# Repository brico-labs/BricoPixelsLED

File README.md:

# BricoPixels LED

PCB diseñanda por BricoLabs para utilizar en proyectos de e-textile. Se utiliza un LED RGB [WS2812B](assets/WS2812B.pdf) el cual incorpora un circuito de control dentro del propio componente, que es un encapsulado 5050.

Para utilizar junto con microcontroladores AVR de Atmel (ATmega, ATtiny) o con la familia ESP de Espressif (ESP8266, etc) 

Cada BricoPixel lleva tan solo dos componentes:

* LED RGB [WS2812B](https://www.tme.eu/es/details/ws2812b-b/leds-smd-de-colores/worldsemi/ws2812b-black/) con encapsulado de color negro.
* Condensador [SMD de 100nF 0805](https://www.tme.eu/es/details/08051c104kat2a/condensadores-mlcc-smd-0805/avx/), para estabilizar la tensión de alimentación del circuito de control del LED RGB.

<div style="text-align:center"></div>

La forma de la placa PCB está diseñada para poder coserla directamente sobre cualquier textil con hilo conductor, o incluso pegarla sobre otras superficies planas.

En el directorio *gerber* se encuentra la PCB ya panelizada y lista para fabricar, en placas de 10 x 10 cm y con 25 unidades de BricoPixel cada una. Para esto se utilizó el software [GerberTools](https://github.com/ThisIsNotRocketScience/GerberTools).

**Se recomienda un grosor de PCB menor o igual a 1 milímetro.** Esto facilita recortar manualmente cada uno de los BricoPixel.

<div style="text-align:center"></div>

----

Esta obra está bajo una [licencia de Creative Commons Reconocimiento 4.0 Internacional (CC-BY)](http://creativecommons.org/licenses/by/4.0/).

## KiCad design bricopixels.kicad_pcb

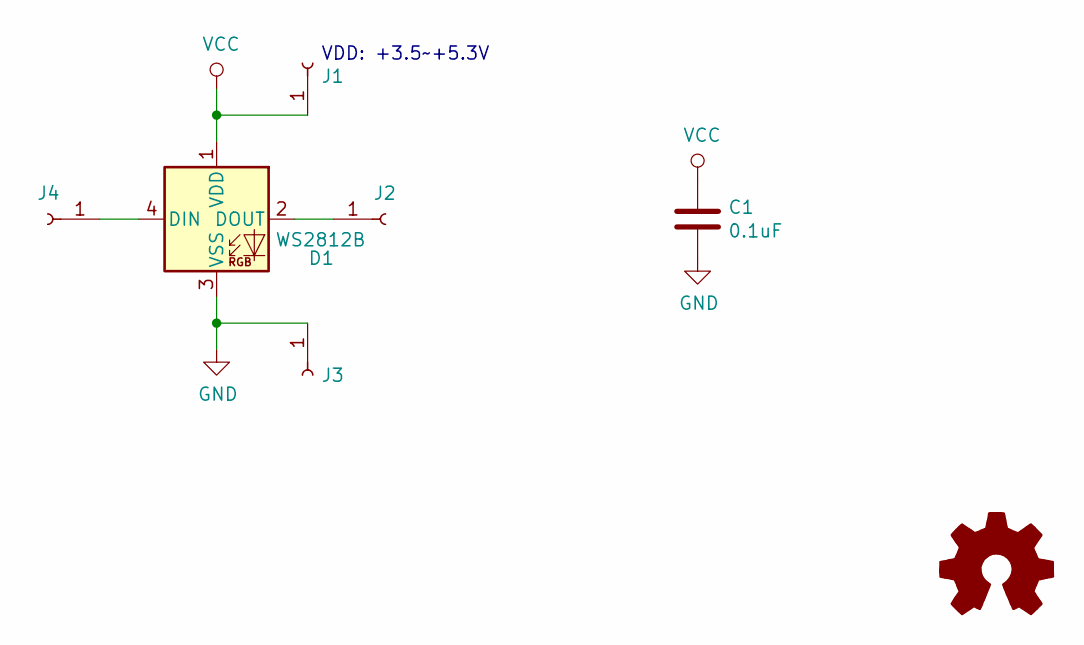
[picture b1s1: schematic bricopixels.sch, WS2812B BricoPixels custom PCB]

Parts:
C1: 0.1uF; C_0805_2012Metric
D1: WS2812B; LED_WS2812B_PLCC4_5.0x5.0mm_P3.2mm
J1, J2, J3, J4: Conn_01x01_Female; BricoPixel_pad_4x

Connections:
GND: C1.2, D1.3 (VSS), J3.1
unnamed: D1.2 (DOUT), J2.1
unnamed: D1.4 (DIN), J4.1
VCC: C1.1, D1.1 (VDD), J1.1

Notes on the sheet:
VDD: +3.5~~+5.3V

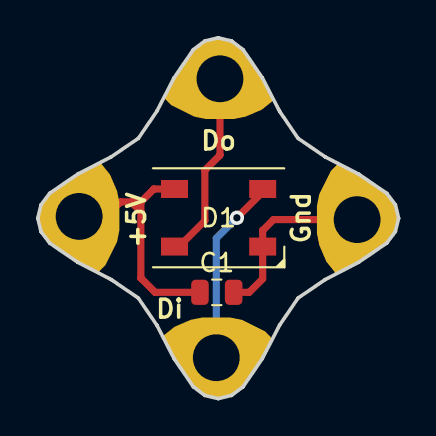
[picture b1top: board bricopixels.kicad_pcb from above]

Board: 2 copper layers, 20.0 x 20.0 mm, 6 parts (0 on the bottom side), 4 nets.

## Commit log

2020-08-10 Uploaded panelizec PCB

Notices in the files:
README.md:
CC BY 4.0
bricopixels.sch:
CC BY-SA
